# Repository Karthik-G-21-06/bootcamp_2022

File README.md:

<div align="center">

</div>

# BOOTCAMP - COIMBATORE
## DAY 1 - INTRODUCTION

On  day one we just had an introductory session on various branches of bi0s hardware like Reversing/Firmware, automotive security, SCADA/ICS, Embedded. Also we had a discussion on how to give pull requests on gitlab also some other commands for gitlabs with the help of this [blog](https://web.archive.org/web/20161121145226/http://rypress.com:80/tutorials/git/index).

## DAY 2 - Reversing/Firmware

On day two we had an interesting session on assembly language and Firmware.Basically assembly language is just a programing language which is older than c and comparatively easier for the computer or processor to understand. These language does not require compiler which converts human readable file into a machine readable file. Instead of variables registers are used. They can store both values and the address of the value. These resiters can be either general purpose,special purpose,instruction pointers,instruction pointers and status flags. Then we discussed about GDB or GNU debugger which is used to reverse an executable file into a human readable program file (mostly assembly language in GDB) which is not the perfect code but just an assumption of how the the file executes and another version peda which just pyhton exploit devolopment assistance for GDB which has some really useful commands for decompiling and understanding the code. The execution of an assembly code is based on stack memory i.e. each fuction creates its own memory stack on top of the main stack which in turn is destroyed itself after the function is completely executed. Furthermore we tried to reverse an exe file. Some challeges were given that are supposed to be reversed.

## DAY 3 - AUTOMOTIVE SECURITY

On day 3 we discussed about automotive security, CAN protocol was on of the crucial protocols that is followed by the microcontrollers or ECUs connected in bus topology such that no host computer is required to communicate with each other. These ECUs or electronic control units are used to control automotive parts like the ABS, stearing, windows etc.these Protocols runs over two wires- CAN-H and CAN-L. This protocol transfers data in an format.
1. indentifier extention: this bit is always zero

2. data frame: this consists of the data which needs to be transferred.

3. Error frame: this frame will be written to specify an error.

4. Arbitration ID: this provides a unique id for each node in the bus.

5. Data length code: represents number of bytes of data.

Then we discussed about ICsim and did some challeges on ICsim like to analyse how the bits change with speed, opening door etc. Finaally challenges were given to do in ICsim.

## DAY 4 - SCADA/ICS

On day 4 we discussed about ICS or industrial control system and SCADA or supervisory control and data acqusition which is used in industries to manage large arrays of machine, with a certain purpose or process, using just a single computer. These machines are connected in a master-slave relation.PLCs and RTUs are acts as the master which could send and request to recieve info to the slaves and sensors etc acts as the slave which does work according the messege from the master to either send  any information or do a perticular function. These messege has certain format or protocol which helps the slaves to understand wheather the messege is for it or not.

## DAY 5 -EMBEDDED SECURITY

Could'nt join on day 5 but read about general hardware  communication protocols like UART, SPI, I2C (I square C) with the help of [wiki bi0s](https://wiki.bi0s.in/hardware/basic-electronics/protocols/). 

 ### UART

 UART or universal asynchronous reciver/transmitter is a hardware communication protocol that uses asynchronous serial communication with configurable speed. Asynchronous means there is no clock signal to sychronize the output bits from transmitting device to receiving device. Two UARTs directly communicate with each other with 2 signals Transmitter(Tx) and receiver(Rx).For communication between 2 UARTs the baut rate should be the same. UART data transmission in done in high voltage. Whenever there is a high to low voltage transition the device starts reading the data frame at the frequency of the baud rate. Data frame contains the actual data being transferred. it can be 5 bits to 8 bits. The data is sent with least significant bit first.
 [source](https://www.analog.com/en/analog-dialogue/articles/uart-a-hardware-communication-protocol.html#:~:text=By%20definition%2C%20UART%20is%20a,going%20to%20the%20receiving%20end.)

 ### SPI

 SPI or serial peripheral interface is a sychronous serial communication interface for short distance communication. SPI device communicate using master-slave architecture with one master and one or more slaves. SPIis a synchronous protocol hence has a clock pin to sync up the data being sent. The data from the master comes through MOSI "master out/slave in" nad the clock s set according the line through whicht the data is transferred. Pins in a SPI device are MOSI, MISO (master in/slave out), SCLK(serial clock), SS(slave select).
 [source](https://wiki.bi0s.in/hardware/basic-electronics/protocols/)

 ### I2C

 I2C or inter-integrated circuit is another sychronous communication protocol used for short distance communication and it supports more than one master and slaves. Each slave can be connected to multiple masters and each master can be connected to multiple slaves. HTey have 2 pins SDA and SCL. SDA or serial data is to send and receive data between master and slave. SCL or serial clock is the line which caries the clock.
 [source](https://www.circuitbasics.com/basics-of-the-i2c-communication-protocol/)

## DAY 6 - PCB DESIGNING

On day 6 we discussed about PCB designing with the help of a platform called [KiCAD](https://www.kicad.org/download/). KiCAD is used for electronic design automation. PCB can be either single layered or double layered i.e. either one copper sheet is used to connect the components or 2 copper sheets are used respectively. Did one PCB with the help of kiran chetan. Challeges were given to be solved.

## DAY 7 - WIRELESS

day 7 was wireless. Couldnt attend the session but read about wireless from [bi0s wiki](https://wiki.bi0s.in/hardware/wireless/introduction/). wireless communication, as the name suggest, to communicate without any wire. NFC, bluetooth, Radio frequency,  Industrially Controlled Wireless Transmission (ZigBee), WLAN or WiFi, cellular network, GPS, SATCOM etc. THese communication have its own vulnerabilities and can be attacked through:
 1. wireless signal replay: the wireless devices does not have a replay security hence a hacker can easily clone or replay a perticular signal which was sniffed using special device to do a perticular function.

 2. wireless signal deception: the sniffer could decipeher the sniffed signal to understand the packet format to further send a packet to do a certain function,

 3. wireless signal hijacking and DoS attack: the users network is blocked pulls the user from a legitimate network to a simulated network and attack the network.

Then challenges were given but have to try doing it.

## DAY 8- SIDE CHANNEL ATTACK

Side channel attack was an interesting topic that we discussed on day 8. It si an attack based on the fundamental factors like time power consumption etc to decipher the file or to access the file. These attack can be based on some general classes like timing attack, Power monitoring attack, voltage fluctuation attack etc. Some examples on how to do it was shown ut no challeges were assigned.

## DAY 9- LAST DAY OF BOOTCAMP

On the last day we had a session on our falcon badge. It is embedded with an esp module. We were able to play 2-3 game using the LED display and aslo had some challeges and easter egg in the badge. The making of such badge was explained and also got a sneak peek on t=our new badge for InCTF 2022. Also we ended our 

 ## CHALLENGES

  1. ### Reversing/Firmware challenge
     The challenge was to decompile  the executable file given and get output "YOU WIN" but was not able to        get the output for all the four files but will try to find out in 2-3 days.
   
  2. ### Automotive security
      1. CHALLENGE-1 
        to sniff out packets I used  can sniffer -c vcan0 to get the packet transferred in ICsim. To dump the         packet transfer log just use `candump -l vcan0`. Now to replay the captured packet use `canplayer -I         dumped_file_name.log`.
      2. CHALLENGE-2
        To go over the limit in speedometer in ICsim, firtly analyse the log file or  sniffed bits to find           which packet changes for accelaration and file the max value. Now just send a packet higher than the         max to go over 100mph. But to make it constant use a while loop in the terminal. In my case `cansend         vcan0 244#0000004196` will go over 100mph but to make it connstant  use the following command:
        
         ```function repeat(){
         for ((i=0;i<$1;i++));
         do eval ${*:2}done
         }
       
       now give the command `repeat 1000 echo cansend vcan0 244#0000004196` for the cansend command to repeat 1000 times so that the speed is constant.
    
   3. ### PCB DESIGNING
       
       The task was to make a PCB of a simple circuit with atleast 1 via and a custom silkscreen behind the PCB. 

       => [challenge.kicad_pcb](https://github.com/Karthik-G-21-06/bootcamp_2022/blob/main/challege.kicad_pcb)

       => [challenge.kicad_sch](https://github.com/Karthik-G-21-06/bootcamp_2022/blob/main/challege.kicad_sch)

   4. ### SCADA
      
      The task was to just follow the instruction given in the [blog](https://www.hackers-arise.com/post/2016/10/31/SCADA-Hacking-Modbus-MasterSlave-Simulation) to make a  small master-slave system using qmodmaster and modpal.
## SUMMARY
 
 I was able to know about a lot of stuff in bi0s hardware. Most of them were interesting but found reversing to be really interesting even though its really tough to understand. Also was able to bond with our senior and also enjoyed the stay at coimbatore even though had some issue. Overall I had a really great time there and will be looking into reversing/firmware. Thanks Bi0s team for organising this really informative and fun bootcamp.

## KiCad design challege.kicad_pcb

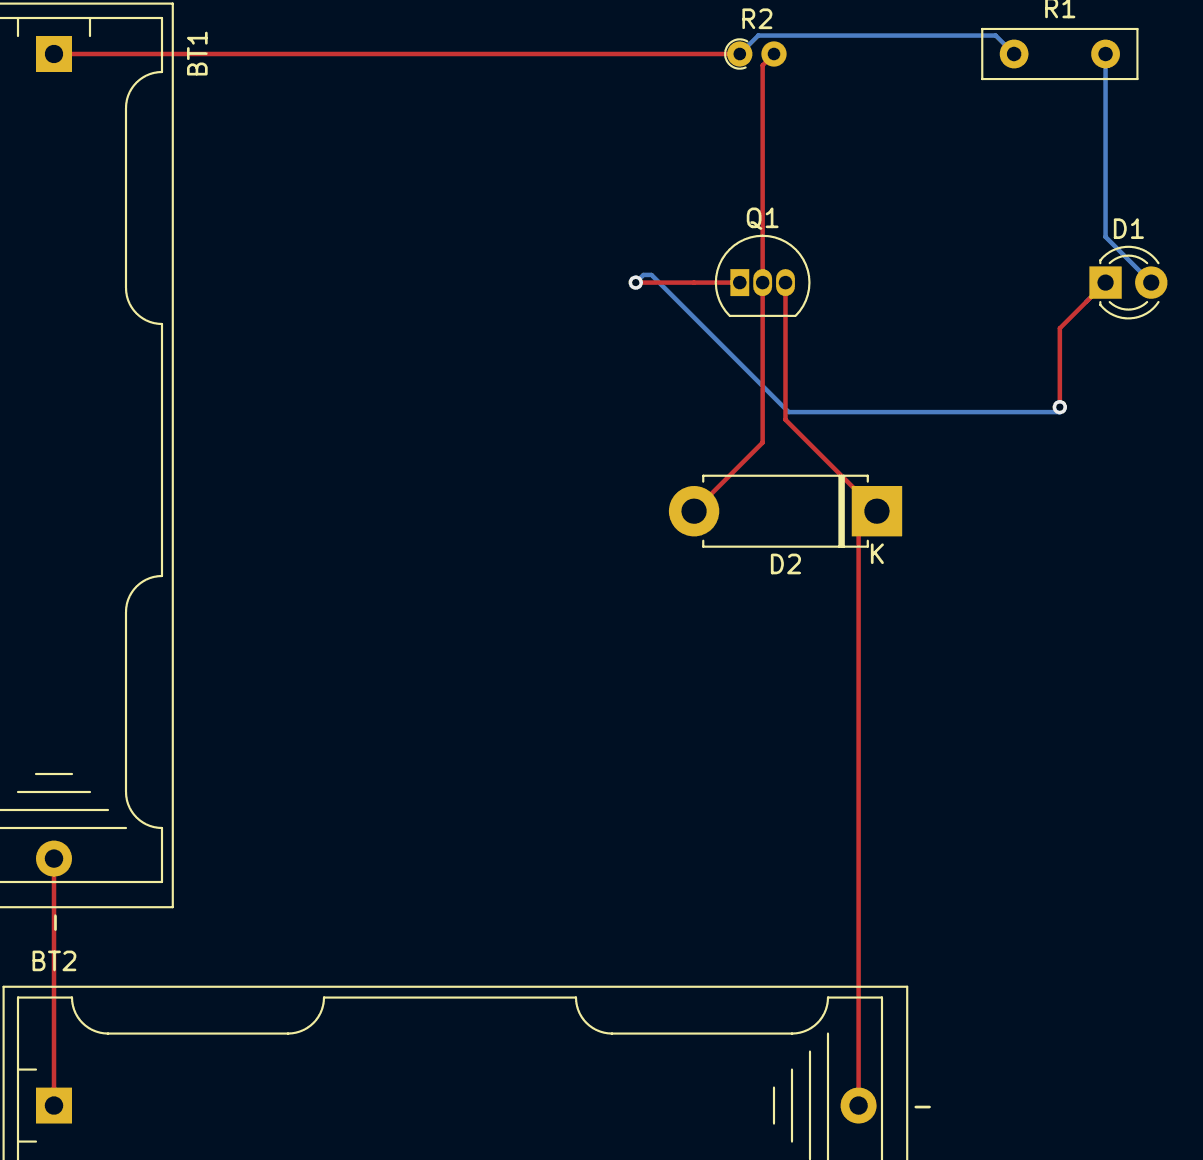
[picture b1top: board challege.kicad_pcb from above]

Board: 2 copper layers, 7 parts (0 on the bottom side), 6 nets.

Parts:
BT1, BT2: 4.5V; BatteryHolder_Keystone_2466_1xAAA
D1: LED; LED_D3.0mm
D2: 1N4148; D_5W_P10.16mm_Horizontal
Q1: BC547; TO-92_Inline
R1: 220; R_Box_L8.4mm_W2.5mm_P5.08mm
R2: 1k; R_Axial_DIN0204_L3.6mm_D1.6mm_P1.90mm_Vertical

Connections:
unnamed: BT1.1 (+), R1.1, R2.1
unnamed: BT1.2 (-), BT2.1 (+)
unnamed: BT2.2 (-), D2.1 (K), Q1.3 (E)
unnamed: D1.1 (K), Q1.1 (C)
unnamed: D1.2 (A), R1.2
unnamed: D2.2 (A), Q1.2 (B), R2.2

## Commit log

2022-08-20 kicad pcb
